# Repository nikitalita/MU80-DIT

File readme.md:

WARNING: WORK IN PROGRESS, COMPLETELY UNTESTED

From https://kurohane.net/wiki/index.php?SC-88Pro%E3%81%AB%E5%85%89%E3%83%87%E3%82%B8%E3%82%BF%E3%83%AB%E5%87%BA%E5%8A%9B%E3%82%92%E4%BB%98%E3%81%91%E3%82%8B

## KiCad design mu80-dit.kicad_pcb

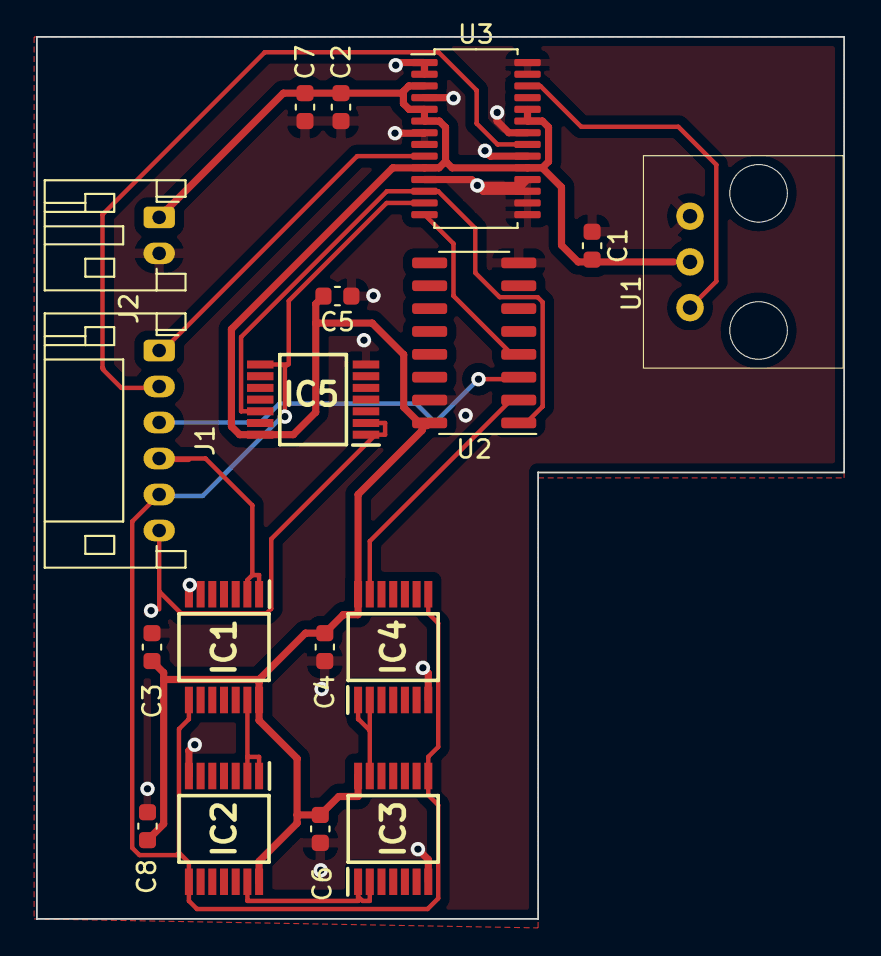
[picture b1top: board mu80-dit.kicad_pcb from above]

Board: 2 copper layers, 44.8 x 49.0 mm, 18 parts (0 on the bottom side), 15 nets.

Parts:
C1, C2, C3, C4, C5, C6, C7, C8: 0.1u/35V; C_0603_1608Metric
IC1, IC2, IC3, IC4, IC5: 74AHC164PW,118; SOP65P640X110-14N
J1: Conn_01x06_Male; JST_PH_S6B-PH-K_1x06_P2.00mm_Horizontal
J2: Conn_01x02_Male; JST_PH_S2B-PH-K_1x02_P2.00mm_Horizontal
U1: TOTX-177L; Toshiba_TOTX177
U2: 74FST3257DTR2G; SOIC-16_3.9x9.9mm_P1.27mm
U3: CS8406; TSSOP-28_4.4x9.7mm_P0.65mm

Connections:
+5V: C1.2, C2.2, C3.2, C4.2, C5.2, C6.2, C7.2, C8.2, IC1.14 (VCC), IC2.14 (VCC), IC3.14 (VCC), IC4.14 (VCC), IC5.14 (VCC), J2.1, U1.2 (VCC), U2.16 (VCC), U3.3 (AD2/~EMPH), U3.5 (TSTN/SFMT1), U3.6 (VD), U3.10 (TEST/APMS), U3.19 (INT/~AUDIO), U3.23 (VL), U3.24 (H/~S)
/BICK: IC1.8 (CP), IC2.8 (CP), IC3.8 (CP), IC4.8 (CP), IC5.8 (CP), J1.5, U3.13 (ISCLK)
/LRCK: IC5.1 (DSA), IC5.2 (DSB), J1.6
/LSI: J1.3, U2.3 (1B2)
/MCLK: J1.2, U3.21 (OMCK)
/RESET: J1.1, U3.9 (~RST)
/RSI: IC1.1 (DSA), IC1.2 (DSB), J1.4
/SDAT: U2.4 (1A), U3.14 (SDIN)
/SHIFT_LRCK: IC5.12 (Q6), U2.1 (S), U3.12 (ILRCK)
/SHIFT_RSI: IC4.13 (Q7), U2.2 (1B1)
/TXP: U1.1 (GND), U3.26 (TXP)
GND: C1.1, C2.1, C3.1, C4.1, C5.1, C6.1, C7.1, C8.1, IC1.7 (GND), IC2.7 (GND), IC3.7 (GND), IC4.7 (GND), IC5.7 (GND), J2.2, U1.3 (Input), U2.8 (GND), U2.15 (~OE), U3.1 (SDA/CDOUT/COPY/C), U3.2 (AD0/~CS/TEST), U3.4 (RXP/SFMT0), U3.7 (TEST), U3.8 (TEST), U3.11 (TEST/TCBLD), U3.15 (TCBL), U3.16 (TEST/CEN), U3.17 (TEST/U), U3.18 (TEST/V), U3.20 (U/HWCK0), U3.22 (GND), U3.27 (AD1/CDIN/HWCK1), U3.28 (SCL/CCLK/ORIG)
unnamed: IC1.13 (Q7), IC2.1 (DSA), IC2.2 (DSB)
unnamed: IC2.13 (Q7), IC3.1 (DSA), IC3.2 (DSB)
unnamed: IC3.13 (Q7), IC4.1 (DSA), IC4.2 (DSB)

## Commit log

2022-07-04 add project files
2023-02-08 update flipflop part
